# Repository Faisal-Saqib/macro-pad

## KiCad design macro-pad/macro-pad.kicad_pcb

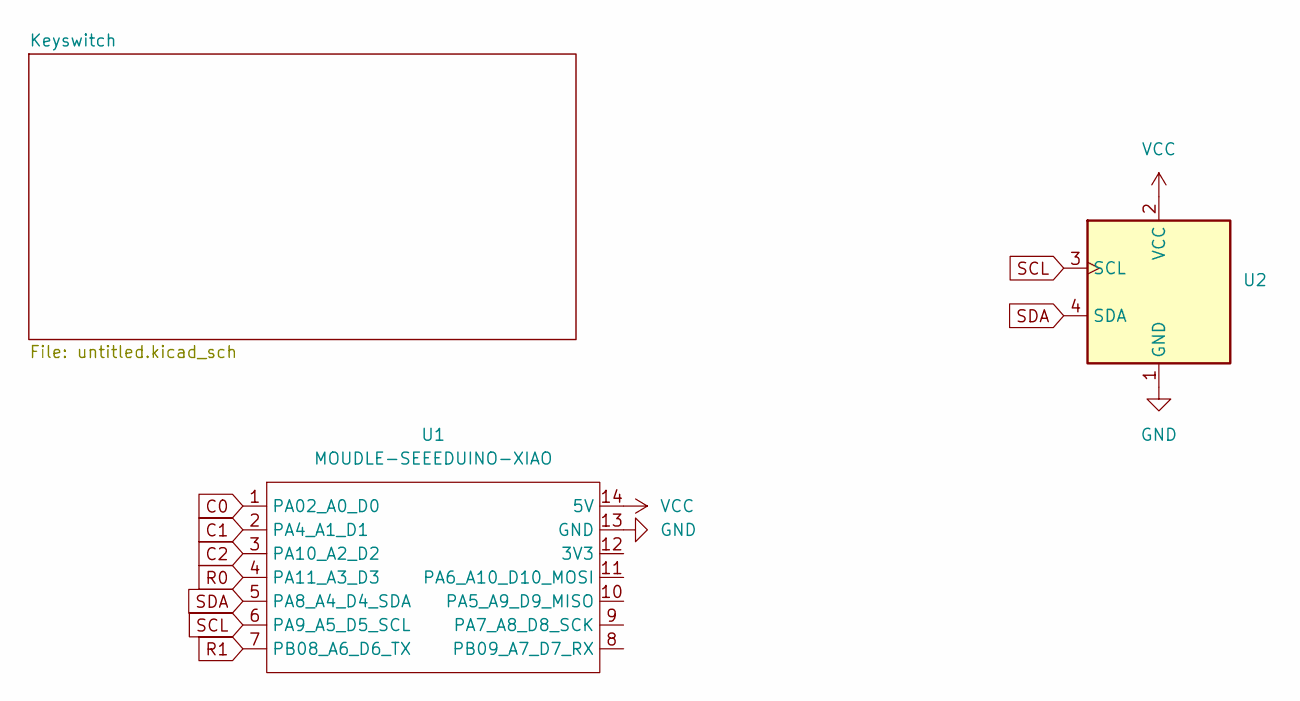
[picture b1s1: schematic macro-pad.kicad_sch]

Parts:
U1: MOUDLE-SEEEDUINO-XIAO; XIAO-Generic-Hybrid-14P-2.54-21X17.8MM
U2: ER_OLEDM0.91_1x-I2C; SSD1306-0.91-OLED-4pin-128x32

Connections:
C0: U1.1 (PA02_A0_D0); also elsewhere on the board
C1: U1.2 (PA4_A1_D1); also elsewhere on the board
C2: U1.3 (PA10_A2_D2); also elsewhere on the board
GND: U1.13 (GND), U2.1 (GND)
INP: U1.14 (5V), U2.2 (VCC)
R0: U1.4 (PA11_A3_D3); also elsewhere on the board
R1: U1.7 (PB08_A6_D6_TX); also elsewhere on the board
SCL: U1.6 (PA9_A5_D5_SCL), U2.3 (SCL)
SDA: U1.5 (PA8_A4_D4_SDA), U2.4 (SDA)

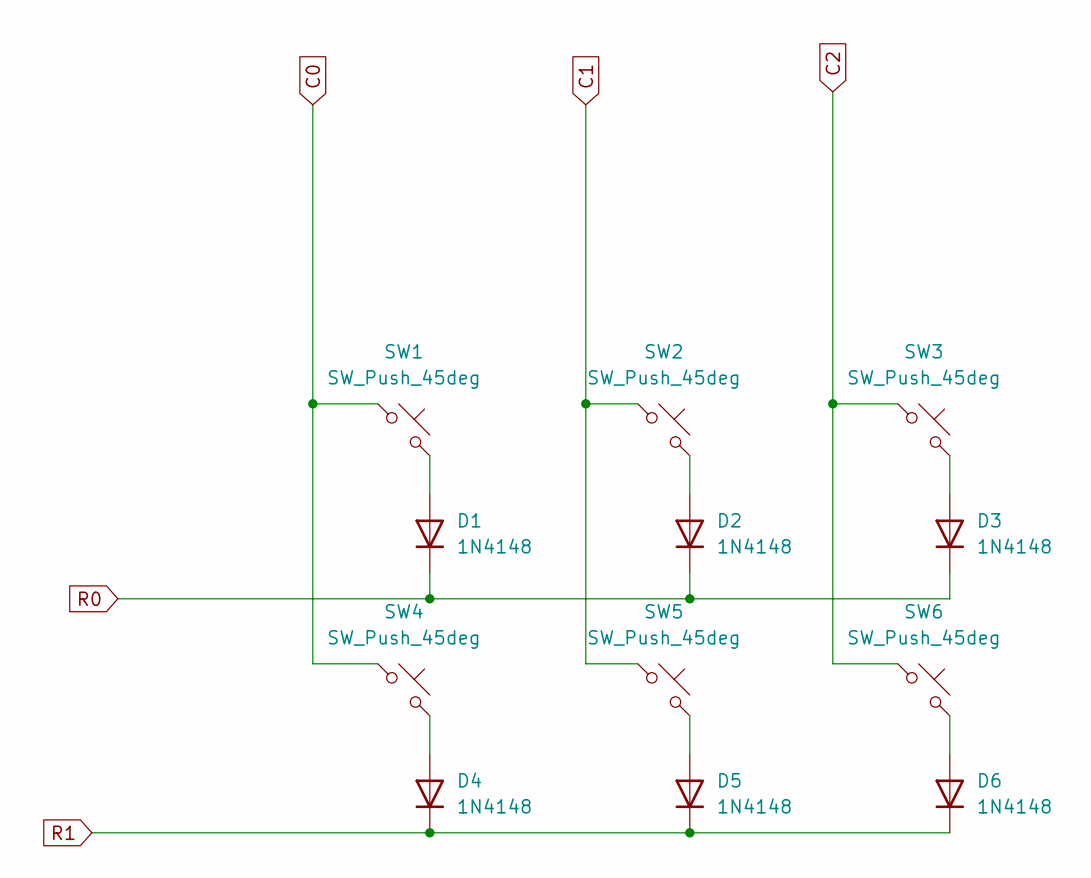
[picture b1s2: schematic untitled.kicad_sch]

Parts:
D1, D2, D3, D4, D5, D6: 1N4148; D_DO-35_SOD27_P7.62mm_Horizontal
SW1, SW2, SW3, SW4, SW5, SW6: SW_Push_45deg; SW_Cherry_MX_1.00u_PCB

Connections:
C0: SW1.1, SW4.1; also elsewhere on the board
C1: SW2.1, SW5.1; also elsewhere on the board
C2: SW3.1, SW6.1; also elsewhere on the board
unnamed: D1.2 (A), SW1.2
unnamed: D2.2 (A), SW2.2
unnamed: D3.2 (A), SW3.2
unnamed: D4.2 (A), SW4.2
unnamed: D5.2 (A), SW5.2
unnamed: D6.2 (A), SW6.2
R0: D1.1 (K), D2.1 (K), D3.1 (K); also elsewhere on the board
R1: D4.1 (K), D5.1 (K), D6.1 (K); also elsewhere on the board

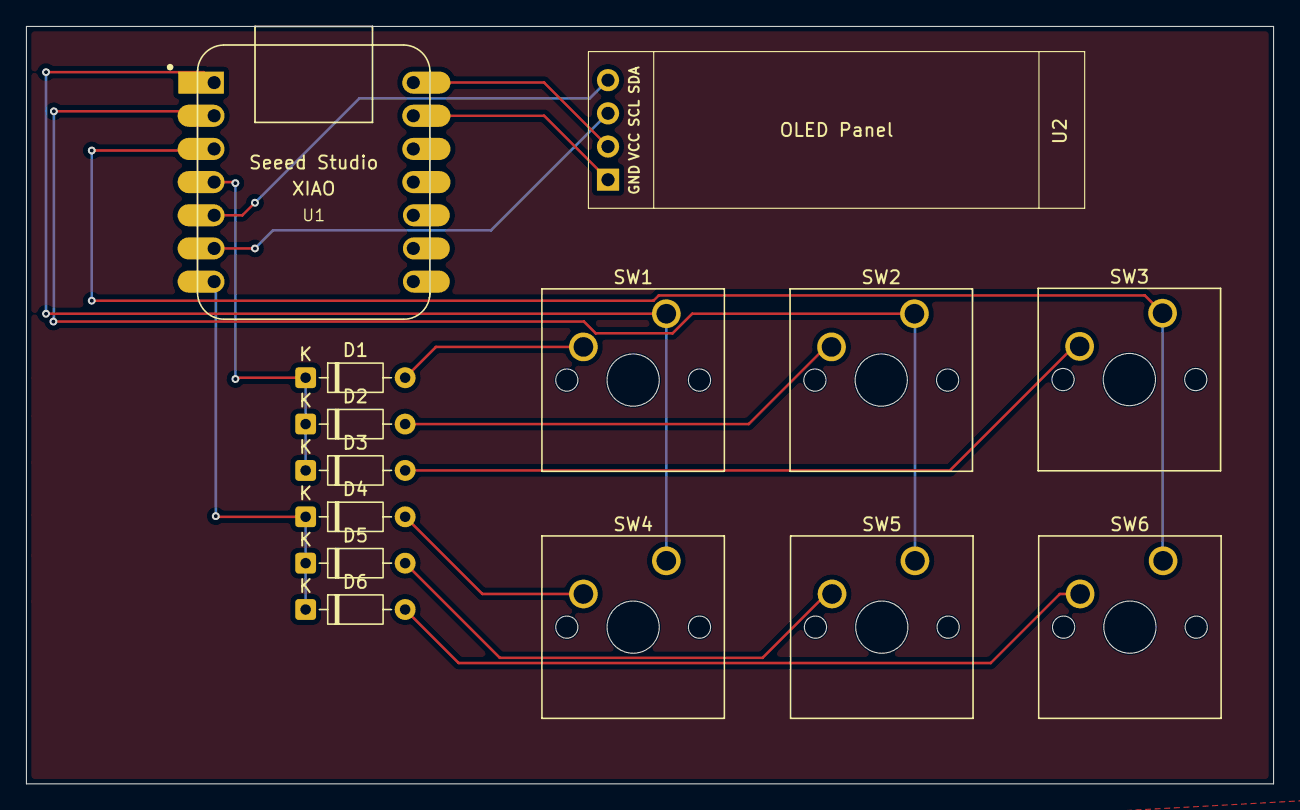
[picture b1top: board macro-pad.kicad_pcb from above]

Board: 2 copper layers, 95.5 x 58.0 mm, 14 parts (0 on the bottom side), 15 nets.
